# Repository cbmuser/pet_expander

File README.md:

# PET 2001N Expander

A simple backplane for the PET 2001N. One unused pin is possibly connected to various linear or low-drop regulators to use a VCC out of the box.

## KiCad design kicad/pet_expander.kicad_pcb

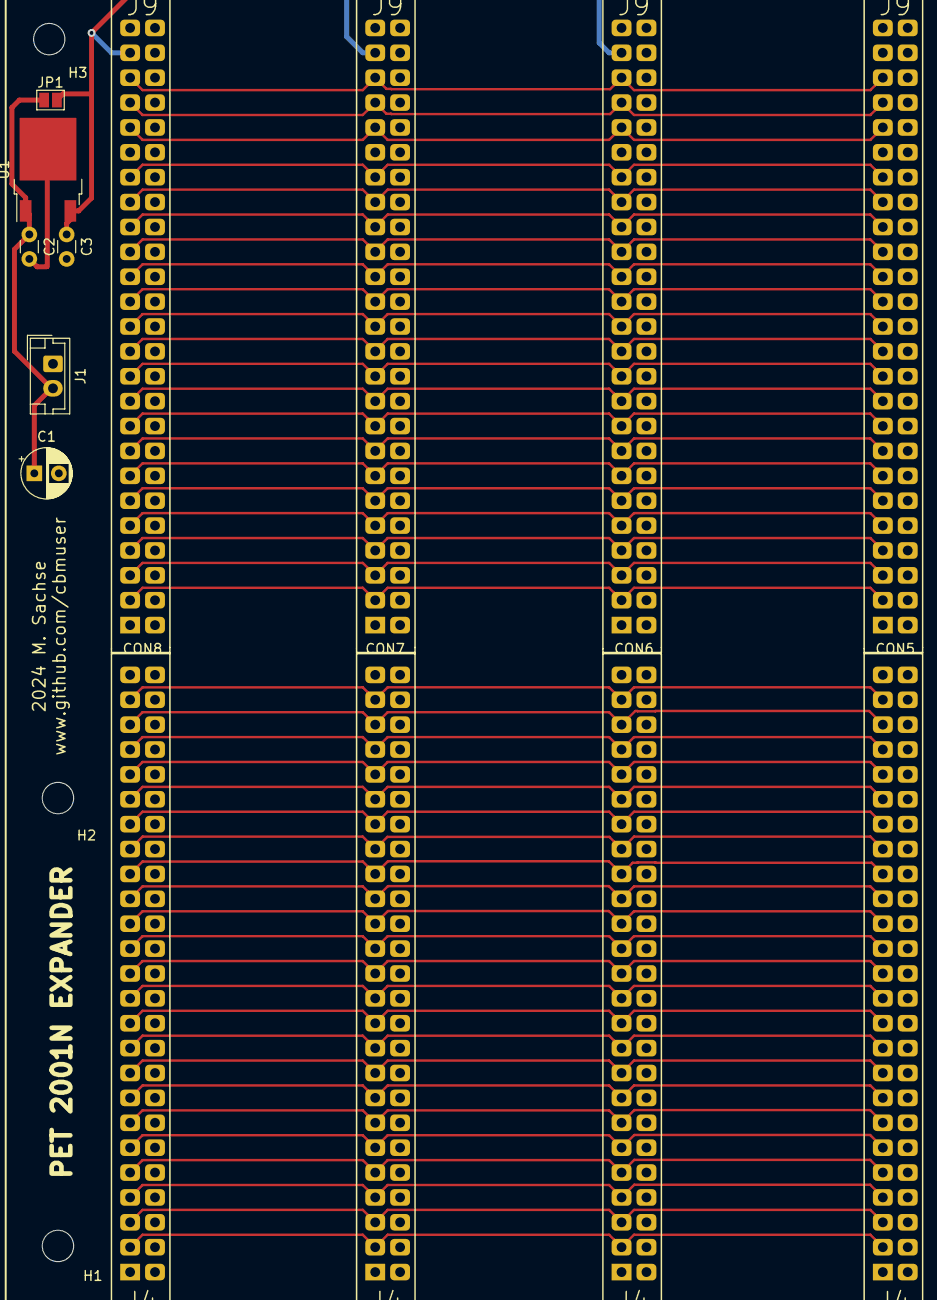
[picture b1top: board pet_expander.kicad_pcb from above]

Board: 2 copper layers, 17 parts (0 on the bottom side), 47 nets.

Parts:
C1: CP; CP_Radial_D5.0mm_P2.50mm
C2, C3: C; C_Disc_D3.0mm_W1.6mm_P2.50mm
CON1, CON2, CON3, CON4: Expansion_J9; PET_EXPANSION_J9
CON5, CON6, CON7, CON8: Expansion_J4; PET_EXPANSION_J4
H1, H2, H3: MountingHole; MountingHole_3.2mm_M3
J1: Conn_01x02; JST_EH_B02B-EH-A_1x02_P2.50mm_Vertical
JP1: Jumper_2_Open; SolderJumper-2_P1.3mm_Open_Pad1.0x1.5mm
U1: LM78M05_TO220; TO-252-2

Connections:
BA0: CON1.2, CON2.2, CON3.2, CON4.2
BA1: CON1.3, CON2.3, CON3.3, CON4.3
BA2: CON1.4, CON2.4, CON3.4, CON4.4
BA3: CON1.5, CON2.5, CON3.5, CON4.5
BA4: CON1.6, CON2.6, CON3.6, CON4.6
BA5: CON1.7, CON2.7, CON3.7, CON4.7
BA6: CON1.8, CON2.8, CON3.8, CON4.8
BA7: CON1.9, CON2.9, CON3.9, CON4.9
BA8: CON1.10, CON2.10, CON3.10, CON4.10
BA9: CON1.11, CON2.11, CON3.11, CON4.11
BA10: CON1.12, CON2.12, CON3.12, CON4.12
BA11: CON1.13, CON2.13, CON3.13, CON4.13
BA12: CON1.14, CON2.14, CON3.14, CON4.14
BA13: CON1.15, CON2.15, CON3.15, CON4.15
BA14: CON1.16, CON2.16, CON3.16, CON4.16
BA15: CON1.17, CON2.17, CON3.17, CON4.17
BD0: CON5.2, CON6.2, CON7.2, CON8.2
BD1: CON5.3, CON6.3, CON7.3, CON8.3
BD2: CON5.4, CON6.4, CON7.4, CON8.4
BD3: CON5.5, CON6.5, CON7.5, CON8.5
BD4: CON5.6, CON6.6, CON7.6, CON8.6
BD5: CON5.7, CON6.7, CON7.7, CON8.7
BD6: CON5.8, CON6.8, CON7.8, CON8.8
BD7: CON5.9, CON6.9, CON7.9, CON8.9
CAS: CON5.21, CON6.21, CON7.21, CON8.21
GND: C1.2, C2.2, C3.2, CON1.1, CON1.25, CON2.1, CON2.25, CON3.1, CON3.25, CON4.1, CON4.25, CON5.1, CON5.25, CON6.1, CON6.25, CON7.1, CON7.25, CON8.1, CON8.25, J1.1, U1.2
NMI: CON5.24, CON6.24, CON7.24, CON8.24
unnamed: C1.1, C2.1, J1.2, JP1.1, U1.1
unnamed: C3.1, CON2.24, CON3.24, CON4.24, JP1.2, U1.3
PHI2: CON1.21, CON2.21, CON3.21, CON4.21
RAS: CON5.20, CON6.20, CON7.20, CON8.20
RDY: CON5.23, CON6.23, CON7.23, CON8.23
RES: CON5.22, CON6.22, CON7.22, CON8.22
RW_: CON1.22, CON2.22, CON3.22, CON4.22
SEL2: CON5.10, CON6.10, CON7.10, CON8.10
SEL3: CON5.11, CON6.11, CON7.11, CON8.11
SEL4: CON5.12, CON6.12, CON7.12, CON8.12
SEL5: CON5.13, CON6.13, CON7.13, CON8.13
SEL6: CON5.14, CON6.14, CON7.14, CON8.14
SEL7: CON5.15, CON6.15, CON7.15, CON8.15
SEL8: CON5.16, CON6.16, CON7.16, CON8.16
SEL9: CON5.17, CON6.17, CON7.17, CON8.17
SELA: CON5.18, CON6.18, CON7.18, CON8.18
SELB: CON5.19, CON6.19, CON7.19, CON8.19
SYNC: CON1.18, CON2.18, CON3.18, CON4.18
_IRQ: CON1.19, CON2.19, CON3.19, CON4.19
_RW: CON1.23, CON2.23, CON3.23, CON4.23

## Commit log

2024-10-20 KiCad and Gerber-Files
